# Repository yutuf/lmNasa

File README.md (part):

# LunaNav — where and when should we land on the Moon?

Open-source planning tool for landing sites and dates at the lunar south pole: describe a mission, and LunaNav
searches the real terrain hour by hour and tells you where and when a solar lander survives. Then stand on the
lander, or drive a rover there.

Two interfaces: **Simple** (pick a mission and a month, get the top sites as cards, open a site's profile) and
**Advanced** (every requirement, the tables, charts, the Artemis comparison and exports); switch at the top.

## In 30 seconds

**The problem.** At the lunar south pole the Sun skims the horizon, so a few hundred metres decide whether a lander
has power, can talk to Earth, can touch down safely, and is near water ice. Today, answering *"where and on which
date do we land?"* takes several expert tools.

**What LunaNav does.** Pick a mission (or describe it to the guide). In a few seconds it checks **21,856 points × every
landing date × every hour** against NASA LOLA terrain and JPL DE440, and ranks where the mission survives:

- **Survives:** sunlight, Earth contact (with a free NASA DSN dish), the longest darkness, and a battery model.
- **Lands safely:** 95 % of the touchdown zone (100 m to 1 km) is gentler than a limit, from LOLA 40 m slopes.
- **Worth it:** the distance to the nearest *ice cold trap* (permanent shadow where Diviner puts ice within 1 m).
- **Gets there:** a spacecraft route from Earth to a polar orbit to the descent, approaching with the Sun behind it.

**One number.** Under a 14-day robotic-lander mission in September 2027, **every centre of NASA's Artemis III
regions inside the search area fails a terrain check, and LunaNav finds landable points 4–13 km away in five of
them.**

**Checked, not assumed.** Sunlight against NASA's own maps (median +1.9 points, r = 0.96); touchdown slopes against
LOLA's official 40 m slope map (median 1.15°, r = 0.94, 6,620 points); this browser engine against the Python
reference (18 cases identical). The full list is in the app under *Method & data*.

### Built during NASA Space Apps 2026 (14–15 Nov)

The project existed before the event: everything up to the git tag `pre-hackathon` (the site search, horizons,
lander and rover views, and the Python planner). Added during the event, all on top of that tag:

| Added | Where |
|---|---|
| Touchdown zone check (LOLA 40 m slopes, 100 m to 1 km zones), validated against LOLA's slope map | `scripts/build_hazard.py`, `web/src/engine.ts` |
| Water ice: distance to the nearest ice cold trap and cold-trap area within 5 km | `scripts/build_science.py` |
| Survival-vs-science chart with the best trade-offs | `web/src/components/TradeOff.tsx` |
| Six mission scenarios, and a simulation that compares them side by side | `web/src/scenarios.ts` |
| Spacecraft route on the globe, with the approach direction chosen against the Sun | `web/src/flight.ts` |
| Artemis III head-to-head: each region's centre against the best point inside it | `web/src/artemis.ts` |
| Ask Luna works with no AI key (an offline guide, EN/TR); Gemini when a key is set | `web/src/lunaLocal.ts` |
| Validation panel, launch window, 3-step guide; zone, ice and approach in the CSV and report | `web/src/App.tsx`, `web/src/report.ts` |

The plan and progress log: [docs/HACKATHON_PLAN.md](docs/HACKATHON_PLAN.md). A 2-minute demo script for the web app: [docs/DEMO_WEB.md](docs/DEMO_WEB.md).

## The web app (`web/`)

```bash
cd web && npm install && npm run dev        # http://localhost:5173
```

Static site (Vite + React + three.js) with one optional serverless function for the AI guide; deploys to Vercel
with root directory `web` (set `GEMINI_API_KEY` for the AI guide). Everything else runs in the browser, offline.

**Search, not a spot picker.** Set the mission (length, minimum sunlight and Earth contact, longest darkness,
battery, steepest ground, whether Earth contact also needs a free NASA DSN dish) and a landing window. A Web
Worker engine checks all 21,856 points of a 2 km grid around the south pole, every landing date in the window,
hour by hour against each point's real LOLA horizon (about 12 million hourly checks in about a second), and
ranks the sites. The same algorithm as the Python package, checked against it case by case (`web/src/*.test.ts`).

- **Results:** a ranked table with place names from the IAU gazetteer ("SE rim of Shackleton", "on Mons
  Malapert"), the share of landing dates that pass, and the Artemis III region each site falls in; CSV export
  and a printable report; tick two to four rows to compare them side by side.
- **Site detail:** a GO / NO-GO verdict with the reason in one sentence; sunlight, Earth contact, longest
  darkness and battery against the requirements; every landing date in the window; the mission's sunrises,
  sunsets and Earth link losses; better spots within 8 km; eclipses inside the mission (Earth hiding the Sun,
  checked against NASA's eclipse catalogue); what the lander sees, as a 360° horizon with the Sun and Earth
  moving over it; and a calendar of every landing date from November 2026 to the end of 2028.
- **Sunlight map:** scrub or play the mission and watch the shadows sweep across the pole.
- **Copy link:** the address keeps the mission and the chosen site.
- **Ask Luna:** describe a mission in your own words ("a 3-week rover landing in spring 2027 that must always
  reach Earth") or ask about the results; an AI guide (Google Gemini, server-side key) sets up the search or
  explains the numbers, using only what the engine computed. English and Turkish throughout.

**Be there.** From any result, *Stand on the lander* or *Drive a rover here*:

- Real LOLA terrain: 10 m maps from NASA's 5 m/px LOLA site models (Barker et al. 2021) at 15 landing areas,
  the 200 m polar grid elsewhere, lunar curvature included; NASA 3D models (Apollo LM, rover, LRO).
- The Sun and Earth where the ephemeris puts them for that date; ridges cast real shadows (a horizon ray-march
  per vertex for distant ridges, a shadow map nearby); dashed paths show where the Sun and Earth travel during
  the mission.
- A survival game with honest physics: battery, solar input and power use, countdowns to sunset and Earth-set,
  radio link through the DSN, time warp to an hour per second. The rover power figures are illustrative and
  labelled as such.
- A VIPER-style objective: drive to the most ice-favourable permanently shadowed spot nearby (NASA permanent
  shadow map, USGS ice index, Diviner temperatures and ice stability depth), drill for two hours, and bring the
  sample back into sunlight before the battery runs out. A route planner (A* over the terrain, rover slope
  limit, prefers sunlit ground) with an autopilot.
- Keyboard and game controller; a USB LED ring can mirror the rover's sky live ([hardware/sky_link](hardware/sky_link)).

### Data in the web app

| What | Source |
|---|---|
| Terrain horizons, 21,856 points | NASA LRO LOLA polar DEMs (PDS), `scripts/build_horizon_atlas.py` |
| Sun and Earth, hourly | JPL DE440 via Skyfield, Moon-fixed, Earth parallax per point |
| Deep Space Network visibility | Goldstone, Madrid, Canberra, 10° mask |
| 10 m rover terrain | LOLA 5 m/px site DEMs, Barker et al. 2021 (NASA GSFC PGDA product 78) |
| Permanent shadow, average Sun/Earth visibility | Mazarico et al. 2011 (PGDA product 69) |
| Ice favorability index | USGS Astrogeology |
| Surface temperature, ice stability depth | LRO Diviner Polar Resource Product (Paige et al., PDS) |
| Place names | IAU Gazetteer of Planetary Nomenclature (USGS) |
| Artemis III regions | NASA / USGS candidate region outlines |
| 3D models | NASA 3D Resources (`web/public/models/CREDITS.md`) |
| Regolith texture | NASA Artemis south-pole simulation kit (USGS 84S project) |

## The Python package and planner (`lunanav/`, `app.py`)

The science lives in a tested Python package; the original Streamlit planner (live at
https://limitlessapps.streamlit.app/) remains for detailed analysis. Demo video of the planner:
[docs/demo/lunanav-demo.mp4](docs/demo/lunanav-demo.mp4).

Existing tools (QuickMap, Moon Trek, JPL Horizons) are built for detailed analysis.
Answering a simple planning question — *"at this south-pole site, on which dates do we
have Sun and Earth in view, and does the lander survive the night?"* — takes many steps
and expert knowledge. LunaNav answers it in one screen:

- **All nine NASA Artemis III candidate regions** (USGS grids) plus published candidate points, each with
  its source.
- **Score heatmap:** every candidate site × every start date, bright = go (colour-blind-safe), readable
  on a phone; filter by site group.
- **Real terrain horizon:** Sun and Earth are compared against the actual LOLA horizon, not a flat one.
- **Battery survival:** a transparent lander power model shows *when* a mission would die.
- **Battery sizing:** the smallest battery that survives the chosen mission (exact for the model),
  plus a GO / NO-GO verdict in plain words and the score broken down term by term.
- **360° view from the lander:** the terrain silhouette with the Sun's and Earth's paths over the
  mission, plus a time slider — *"on day 5, is the Sun up, and when does it set?"*
- **Communication windows:** when Earth is above the terrain, and when it next sets or rises.
- **English / Türkçe:** a switch at the top translates the simple view (the planner stays in English);
  `?lang=tr` opens the page in Turkish.
- **Anywhere on the Moon:** a whole-Moon relief map and 16 landed missions (Luna 9 to Blue Ghost 1,
  `data/landed_missions.yaml`); outside the south pole the horizon is traced from LOLA's global grid
  (`data/global_grid.npz`, 1.9 km). Sun and Earth tracks are rotated from a computed site with Earth's parallax
  corrected from the hourly Earth-Moon distance (`lunanav/anywhere.py`): checked against independent DE440 runs
  2,700 km away, within 0.018° (without the parallax correction Earth would be off by 0.33°); `tests/test_anywhere.py`.
- **Any point near the pole:** pick a spot south of 84.5°S on a LOLA relief map (or type its coordinates); the
  app traces its horizon on the spot from a compact 200 m / 800 m LOLA grid (`data/polar_grid.npz`, 5 MB) and
  rotates the Sun/Earth track from the nearest computed site. Against the full-resolution horizons at 27 sites:
  sunlit share within 0.5 points (median, worst 4.1), Earth in view within 0.0 (median, worst 13.9 on a narrow
  crest); `tests/test_polar_grid.py`.
- **Deep Space Network check:** Earth above the lander's horizon is not enough; one of NASA's DSN complexes
  (Goldstone, Madrid, Canberra) must also see the Moon. Precomputed hourly (`data/dsn.npz`): each complex sees
  the Moon above 10° about 41 % of the time, at least one of them 98.3 % of the time.
- **Simple view first:** the page opens on one question, five landing spots, a large GO / NO-GO with the reason in
  one sentence, a day-by-day strip, what happens if the launch slips (1 day to 1 month), the same date at the
  other spots, and an animation of the Sun and Earth moving along the real horizon, and a 3D view of the 40 × 40 km of terrain
  around the lander with the shadows the Sun casts at any hour of the mission (`data/terrain/`, cut from LOLA
  by `scripts/make_terrain_patches.py`; shadows from terrain inside the patch only, see `lunanav/terrain3d.py`).
- **Cited vs derived points:** every site comes from a publication: a published point, or the centre of an official
  Artemis III region computed from the USGS grid (source shown).
  Next to it LunaNav can show a **derived** point (the best spot within 1 km on a gentle slope) and, for
  Artemis III regions, the **best point in the whole region**. Always labelled, never a replacement for
  the cited one.
- **South-pole map** of the sites and NASA's nine Artemis III candidate regions (exact USGS grid
  outlines), true to scale, with the Earth-facing side marked.
- **Shareable links:** the page address always encodes the scenario (settings, which site groups are shown,
  site, start date).
- **CSV export** of any mission: hourly Sun/Earth position, terrain, visibility and battery.
- **Plain-language help** in the app for students, educators and the public, and four ready-made
  classroom activities with answers: [docs/EDUCATORS.md](docs/EDUCATORS.md).
- **2-minute demo script** with a link per scene, every verdict checked in CI: [docs/DEMO.md](docs/DEMO.md).
- **Physical twin** (design stage, not yet manufactured): a true-scale 3D-printable relief of Malapert
  Massif with the three demo points, and a 24-LED "horizon compass" PCB that replays a site's Sun and
  Earth directions from LunaNav's data: [hardware/README.md](hardware/README.md).

## Results at a glance

Data: JPL DE440 + LOLA terrain, hourly, 1 Nov 2026 – 31 Dec 2028; "Sun+Earth" = share of hours with at
least half the Sun's disk and Earth's centre above the terrain, seen from a 2 m mast.

- **All nine NASA Artemis III candidate regions are covered** (USGS grids), plus published points
  (Shackleton connecting ridge, de Gerlache rim, Malapert, IM-2 on Mons Mouton) and Apollo 11 for reference.
- **Region centres are poor stand-ins:** Sun+Earth at the centres ranges from 2 % (Slater Plain) to 28 %
  (Nobile Rim 2). Searching each whole region finds ground with **35 % to 84 %** on slopes ≤ 6°, best at
  Malapert Massif (83.6 %, Earth in view all the time), then Mons Mouton (72.5 %) and Nobile Rim 1 (67.9 %).
- **Terrain beats latitude:** at Malapert, moving 447 m from the published point takes Earth visibility
  from 44 % to 100 %.
- **Checked against NASA's independent maps** (Mazarico et al. 2011): for points nobody optimised the
  median difference is +1.9 points (r = 0.957 over 32 points). LunaNav's best-in-region values are
  matched by NASA's own values within ~100 m (median +0.5 points), since the two terrain models place
  narrow crests slightly differently; read them as the upper end of what NASA's maps support. One Earth
  value (Mons Mouton best point, 60 m map) is still unexplained.
- **Found along the way:** the IM-2 landing point lies in the Mons Mouton *Plateau* region, not the
  Mons Mouton one; NASA's regions overlap (e.g. 136 km² shared by Mons Mouton and the Plateau).
- **Limits:** illustrative lander (not a real spacecraft); slope from a 40 m map, so boulders and small
  craters are invisible; no thermal model or relay satellites.

## How it works

```
offline (needs kernels + DEM)                           runtime (Streamlit, light)
──────────────────────────────                          ──────────────────────────
LOLA south-pole DEM ──► build_horizons.py ──► data/horizons.json ─┐
                                                                  ├─► precompute.py ──► data/series/<site>.npz ──► app.py
NAIF kernels (DE440 + Moon frames) ──► lunanav.ephemeris ─────────┘                         (scoring, battery, plots)
                                                                                     │
LOLA DEM + data/series/<cited>.npz ──► derive_best_points.py ──► data/derived_sites.yaml + <site>_derived.npz
USGS Artemis III grids ──► artemis_regions.py ──► region centres (sites.yaml) + outlines (artemis_regions.json)
LOLA DEM + USGS grids + series ──► derive_region_best.py ──► <site>_region_best (derived_sites.yaml + .npz)
```

`derive_best_points.py` needs only the DEM: the Sun and Earth are so far away that moving
1 km on the Moon changes their direction by < 0.0002°, so the cited site's Sun/Earth alt-az series is
rotated into each candidate's local frame instead of re-running the ephemeris. (Checked against
independent DE440 runs: reprojecting Shackleton ridge → de Gerlache rim, ~25 km, matches to 0.0005° in
altitude.)

The app never touches the DEM or the kernels: everything it reads is committed under `data/`, so it
runs from a plain `pip install -r requirements.txt` with no secrets or API keys (see [Deploy](#deploy)).

| module | job |
|---|---|
| `lunanav/geometry.py` | great-circle steps, elevation angle with lunar curvature, visible disk fraction |
| `lunanav/horizon.py` | ray-march DEM → 360° horizon profile per site |
| `lunanav/ephemeris.py` | Skyfield: Sun/Earth alt-az from a point in the Moon's ME frame (with libration) |
| `lunanav/visibility.py` | Sun disk fraction above terrain, Earth above terrain |
| `lunanav/power.py` | battery state-of-charge simulation |
| `lunanav/metrics.py` | window metrics, constraints, score, vectorised start-date scan, delay tolerance, set/rise timers |
| `lunanav/panorama.py` | azimuth helpers for the 360° view (circular mean, unwrap, compass ticks) |
| `lunanav/derive.py` | candidate grid, slope, alt-az reprojection, ranking for derived points |
| `lunanav/outlines.py` | region outlines at runtime (pure numpy): which Artemis III region(s) contain a point |
| `lunanav/regions.py` | USGS region grids: exact inside/outside test, grid points, projection |
| `lunanav/sites.py` | cited sites (`data/sites.yaml`) + generated derived points (`data/derived_sites.yaml`) |
| `app.py` | Streamlit UI |

| script (offline) | needs | writes |
|---|---|---|
| `scripts/fetch_kernels.py` | internet (NAIF) | `data/kernels/` (DE440 + Moon frames) |
| `scripts/build_horizons.py` | LOLA DEM | `data/horizons.json` |
| `scripts/precompute.py` | kernels + `horizons.json` | `data/series/<site>.npz` |
| `scripts/derive_best_points.py` | LOLA DEM + series | `data/derived_sites.yaml`, `<site>_derived.npz`, horizons |
| `scripts/artemis_regions.py` | USGS grid shapefiles | Artemis III region centres in `data/sites.yaml` |
| `scripts/derive_region_best.py` | LOLA DEM + USGS grids + series | best point inside each region (`<site>_region_best`) |
| `scripts/mazarico_compare.py` | NASA PGDA illumination + PSR maps | `data/mazarico.json`: independent check + nearest permanent shadow |
| `scripts/check_map_alignment.py` | two NASA maps | best registration shift between them (diagnostic) |
| `scripts/make_demo_series.py` | nothing | synthetic series for UI work only (clearly flagged in the app) |
| `scripts/make_global_grid.py` | LOLA `ldem_16.img` | `data/global_grid.npz` for horizons anywhere |
| `scripts/precompute_earth_distance.py` | kernels | `data/earth_distance.npz` for Earth parallax |
| `scripts/make_polar_grid.py` | LOLA 85°S 40 m + 80°S 80 m `.img` | `data/polar_grid.npz` for horizons at any point |
| `scripts/make_terrain_patches.py` | LOLA 85°S 40 m `.img` | `data/terrain/<site>.npz` for the 3D view |
| `scripts/precompute_dsn.py` | kernels | `data/dsn.npz`: Moon elevation at the three DSN complexes, hourly |
| `scripts/make_relief.py` | PDS LOLA polar `.img` | 3D-printable terrain tile (`hardware/relief/*.stl` + site positions) |
| `scripts/export_compass_track.py` | a site's series | LED animation for the horizon compass (`firmware/track.h`) |

## Quick start

```bash
python -m venv .venv && source .venv/bin/activate
pip install -e ".[offline,dev]"
pytest -q          # unit tests, an app smoke test, and integrity checks on the committed data

# real data
python scripts/fetch_kernels.py                          # ~130 MB (DE440)
python scripts/build_horizons.py data/dem/<lola_south_pole>.tif
python scripts/precompute.py      # default window 2026-11-01 → 2028-12-31 23:00 UTC (--end 2029-01-01 is exclusive)
python scripts/derive_best_points.py data/dem/LDEM_80S_40MPP_ADJ.TIF   # optional: derived points

# or synthetic data just to work on the UI
python scripts/make_demo_series.py

streamlit run app.py
```

## Deploy

**Web app (Vercel, free):** import `yutuf/lmNasa` at https://vercel.com/new, set *Root Directory* to `web`
(Vite is detected; build `npm run build`, output `dist`), and add the environment variable `GEMINI_API_KEY`
(a free key from https://aistudio.google.com) for the Ask Luna guide; without it everything except Luna works.
Locally the key goes in `web/.env.local` (git-ignored).

**Streamlit planner:** the planner runs on Streamlit Community Cloud at **https://limitlessapps.streamlit.app/**, deployed from this repo's `main` branch.
Locally: `streamlit run app.py`, then open `http://localhost:8501/`.

To deploy a copy (free; needs a GitHub account, and the sign-in can only be done by a person):

1. Sign in at https://share.streamlit.io with GitHub and allow access to `yutuf/lmNasa`.
2. Create app → repository `yutuf/lmNasa`, branch `main`, main file `app.py`.
3. Under Advanced settings pick Python 3.13 (what CI tests); no secrets are needed.
4. Deploy. Dependencies come from `requirements.txt`; the app imports `lunanav/` from the repo root.

## Adding sites

Every site needs a source. Two ways in:

1. **A published point:** add it to `data/sites.yaml` with `source:` (link) and `verified: true` once the
   numbers are copied from that source.
2. **NASA's Artemis III candidate regions** (published as areas of ~20 × 20 km and larger, not points):
   download the USGS navigation grids ([McClernan 2024, doi:10.5066/P1MEQ6UK](https://doi.org/10.5066/P1MEQ6UK)),
   unzip, then `python scripts/artemis_regions.py <folder> --outlines` (`--outlines` also writes the
   region outlines the map draws, `data/artemis_regions.json`). It adds the area-weighted centre of each
   region's 1 km grid as a site, labelled *region centre* (Malapert Massif keeps its published point,
   which lies inside its region; the IM-2 point is inside the Mons Mouton *Plateau* region, so it does
   not stand in for the Mons Mouton region).

Then rebuild the data for the new sites (needs the DEM and kernels):

```bash
python scripts/build_horizons.py data/dem/LDEM_80S_40MPP_ADJ.TIF --sites <new ids>      # other profiles kept
python scripts/precompute.py --sites <new ids>                                          # other series kept
python scripts/derive_best_points.py data/dem/LDEM_80S_40MPP_ADJ.TIF --sites <new ids>
```

Without `--sites` every site is recomputed. `precompute.py --end` is exclusive.

## Scoring

For one site and one start date, over the mission duration (1 h steps):

- **sunlit** = share of hours with ≥ 50 % of the solar disk above terrain
- **Earth in view** = share of hours with Earth's center above terrain
- **longest shadow** = longest continuous run of non-sunlit hours
- **battery margin** = (min state of charge − failure line) / (1 − failure line)

`score = 100 × (0.4·sunlit + 0.3·Earth + 0.3·battery margin)`.
If any constraint fails (min sunlit, min Earth, max shadow, battery), the score is ×0.25 and the
reasons are listed. Constraints are editable in the sidebar; the weights live in `MissionConstraints`.

Ties at the top are broken by **delay_ok_days**: how many days the launch can slip with every
later start still feasible.

## Derived points

For each cited, non-reference site: a grid of candidates (100 m spacing) within 1 km, candidates
steeper than 10° (40 m baseline) dropped, a full 360° horizon for each, then ranked by the share of
hours with the Sun (≥ 50 % of the disk) **and** Earth in view; tie-break on sunlight. The cited point
is recomputed with the same DEM and settings so the comparison is fair. If no candidate beats the
cited point, no derived point is written. All three numbers are command-line options.

Result with LOLA `LDEM_80S_40MPP_ADJ`, 2026-11-01 → 2028-12-31 (share of hours):

| cited site | cited: Sun+Earth / Sun / Earth / slope | derived point | derived: Sun+Earth / Sun / Earth / slope |
|---|---|---|---|
| Shackleton connecting ridge | 51.8 % / 91.1 % / 53.9 % / 0.7° | — (cited point is already the best) | — |
| de Gerlache rim (site 011) | 41.3 % / 77.3 % / 57.3 % / 3.4° | 200 m W | 48.8 % / 85.2 % / 57.3 % / 1.6° |
| Malapert Massif | 15.8 % / 42.3 % / 44.1 % / **10.5°** | 447 m NE | 66.8 % / 66.8 % / 100 % / 3.9° |
| Mons Mouton (IM-2) | 38.6 % / 45.5 % / 82.1 % / 2.5° | 825 m S | 43.9 % / 51.5 % / 83.7 % / 1.6° |

The Malapert point is published only to whole degrees (86°S, 0°E: ±0.5° ≈ ±15 km in latitude,
≈ ±1 km in longitude at 86°S), so a 447 m move is well inside its own uncertainty; its cited
coordinate is also steeper than our 10° limit, which the app flags.

**Artemis III region centres** (centre of each region's USGS 1 km grid; Malapert Massif uses its
published point above, which lies inside its region. The IM-2 point above lies in the Mons Mouton
*Plateau* region, so the Mons Mouton region has its own centre):

| region centre | centre: Sun+Earth / Sun / Earth / slope | derived point | derived: Sun+Earth / Sun / Earth / slope |
|---|---|---|---|
| Peak near Cabeus B | 9.1 % / 37.9 % / 28.8 % / **12.0°** | 943 m NE | 48.3 % / 63.8 % / 77.0 % / 6.8° |
| Mons Mouton Plateau | 20.2 % / 26.1 % / 66.7 % / 2.1° | 1000 m SW | 40.3 % / 46.3 % / 84.7 % / 8.4° |
| Nobile Rim 2 | 28.1 % / 40.8 % / 65.1 % / 4.7° | 1000 m NE | 31.7 % / 46.6 % / 66.0 % / 7.0° |
| Nobile Rim 1 | 9.4 % / 29.2 % / 32.2 % / **16.9°** | 985 m SE | 26.5 % / 50.2 % / 48.1 % / 5.7° |
| de Gerlache Rim 2 | 21.7 % / 37.2 % / 51.3 % / **11.3°** | 500 m NW | 22.0 % / 37.5 % / 51.3 % / 10.0° |
| Haworth | 6.1 % / 10.0 % / 39.6 % / 2.9° | 1000 m SE | 20.7 % / 36.7 % / 50.9 % / 7.2° |
| Slater Plain | 2.0 % / 2.3 % / 36.7 % / 3.4° | 1000 m SE | 9.6 % / 21.5 % / 40.6 % / 9.8° |
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
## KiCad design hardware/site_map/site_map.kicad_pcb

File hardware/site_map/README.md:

# Site map: a PCB map of the lunar south pole

A 100 x 100 mm two-layer board. The silkscreen is a south polar stereographic map with the nine
Artemis III candidate regions, and one WS2812B LED sits at each region's best landing point as computed
by LunaNav (`data/derived_sites.yaml`), plus two published points from `data/sites.yaml`. Firmware, which
does not exist yet, is meant to colour each LED by the GO / NO-GO verdict for a chosen landing date.

Nothing here has been manufactured or powered.

## Rebuild

```
"C:/Program Files/KiCad/10.0/bin/python.exe" hardware/site_map/generate_board.py
cd hardware/site_map
kicad-cli pcb drc --refill-zones --save-board --severity-error --severity-warning --output drc_report.txt site_map.kicad_pcb
kicad-cli pcb render --output render_top.png --side top --width 1400 --height 1400 --quality high --background opaque site_map.kicad_pcb
kicad-cli pcb export step --subst-models --force -o site_map.step site_map.kicad_pcb
```

There is no schematic: `generate_board.py` is the netlist. It places the parts, routes the board with its
own grid router, draws the silkscreen and writes `led_sites.json`. `site_map.kicad_pro` is the file
kicad-cli created with its defaults; no rule or severity in it was edited.

## Map

- Projection: south polar stereographic on a sphere of radius 1737.4 km, r = 2 R tan((90 + lat) / 2),
  x = r sin(lon), y = r cos(lon). Longitude 0 (Earth side) points up, 90 E points right.
- Scale 1:4,000,000 (4 km per mm). The pole is at (53.0, 53.0) mm from the board's top-left corner.
- Check: the published Malapert point (86.0 S, 0 E) projects to x = 0.000 km, y = +121.343 km, straight
  above the pole.
- The nine region outlines span 89.3 x 59.4 mm on the board; margins to the board edge are 5.46 mm left,
  8.73 mm top, 5.25 mm right.
- Silkscreen: region outlines, dashed latitude circles at 85 S and 88 S with labels, a cross at the pole,
  an EARTH arrow pointing up, a 50 km scale bar (12.5 mm), the scale, the title, one label per LED.

## LEDs

Chain: J1 pin 2 (DIN) -> R1 330 ohm -> D1 ... D11 -> J2 pin 2 (DOUT). Chain index = D number - 1.
Positions in mm from the board's top-left corner. The full table with lat, lon and true positions is in
`led_sites.json`.

| Ref | Site id | Placed (mm) | Offset from true position |
| --- | --- | --- | --- |
| D1 | shackleton_ridge (published) | 50.11, 56.12 | 0 |
| D2 | de_gerlache_rim (published) | 51.99, 47.16 | 8.60 mm = 34.4 km |
| D3 | artemis_de_gerlache_rim_2_region_best | 43.09, 48.95 | 0 |
| D4 | artemis_peak_near_cabeus_b_region_best | 7.89, 35.30 | 0 |
| D5 | artemis_haworth_region_best | 42.14, 27.67 | 0 |
| D6 | malapert_massif_region_best | 51.77, 22.44 | 0 |
| D7 | artemis_mons_mouton_region_best | 66.15, 23.90 | 5.20 mm = 20.8 km |
| D8 | artemis_nobile_rim_1_region_best | 75.12, 22.97 | 0 |
| D9 | artemis_mons_mouton_plateau_region_best | 84.68, 20.44 | 0 |
| D10 | artemis_nobile_rim_2_region_best | 90.74, 29.19 | 0 |
| D11 | artemis_slater_plain_region_best | 69.26, 65.67 | 0 |

Two LEDs are not on their true position, because the generator keeps LED centres at least 9.0 mm apart
(room for the 100 nF capacitor and vias of each LED; the smallest distance on the board is 9.02 mm):

- D7, Mons Mouton region best: moved 20.8 km. A leader line runs to a dot at the true position, which is
  just left of D8. One silkscreen line of D8's footprint was removed so that it does not touch the dot.
- D2, published de Gerlache rim point: moved 34.4 km. Its true position lies under D3 (the de Gerlache
  Rim 2 region-best LED), so no dot can be drawn; the leader line ends at D3.

## Electrical

- 11 x WS2812B 5050, 11 x 100 nF 0603 (one next to each LED's VDD pad), R1 330 ohm 0603 in series with
  the data input, J1 1x3 2.54 mm header (5V, DIN, GND) and J2 1x3 header (5V, DOUT, GND) at the bottom
  edge, 4 M3 holes 5 mm in from the corners.
- Data chain: 217.5 mm of 0.25 mm track in 13 nets, all on the front layer, no vias, longest hop 38.5 mm.
- +5V: 0.5 mm stubs on the front, one via per LED, and a 0.8 mm bus on the back layer in chain order from
  J1 to J2 (268.1 mm).
- GND: pours on both layers, two GND vias per LED.
- DRC (`drc_report.txt`, errors and warnings): 0 violations, 0 unconnected items.

## Not verified, and known weaknesses

- Nothing has been built, soldered or powered. No firmware exists for this board.
- At this scale a typical region is only a few millimetres across, smaller than the 5 mm LED sitting in
  it. Silkscreen lines are cut where they cross pads and footprint outlines, so most region outlines are
  partly or fully hidden under their LED in `render_top.png`. A larger board or smaller LEDs (2020 size)
  would be needed to show every outline in full.
- The LED labels carry short names (for example "DG RIM 2"); the regions have no separate name labels.
- The pole cross is cut short where it meets D1's pad.
- The +5V bus is a single 0.8 mm daisy chain, not checked for voltage drop with all 11 LEDs at full white
  (roughly 0.66 A by the usual 60 mA per LED figure, which is a datasheet-level assumption, not measured).
- The script reads the YAML files with its own small parser (KiCad's Python has no PyYAML); the result was
  not cross-checked against PyYAML.
- The STEP file was exported but not opened in a CAD program. `--subst-models` was used; whether every
  part has a 3D model in it was not checked.
- Only the top render was inspected. The back layer was checked by DRC only.

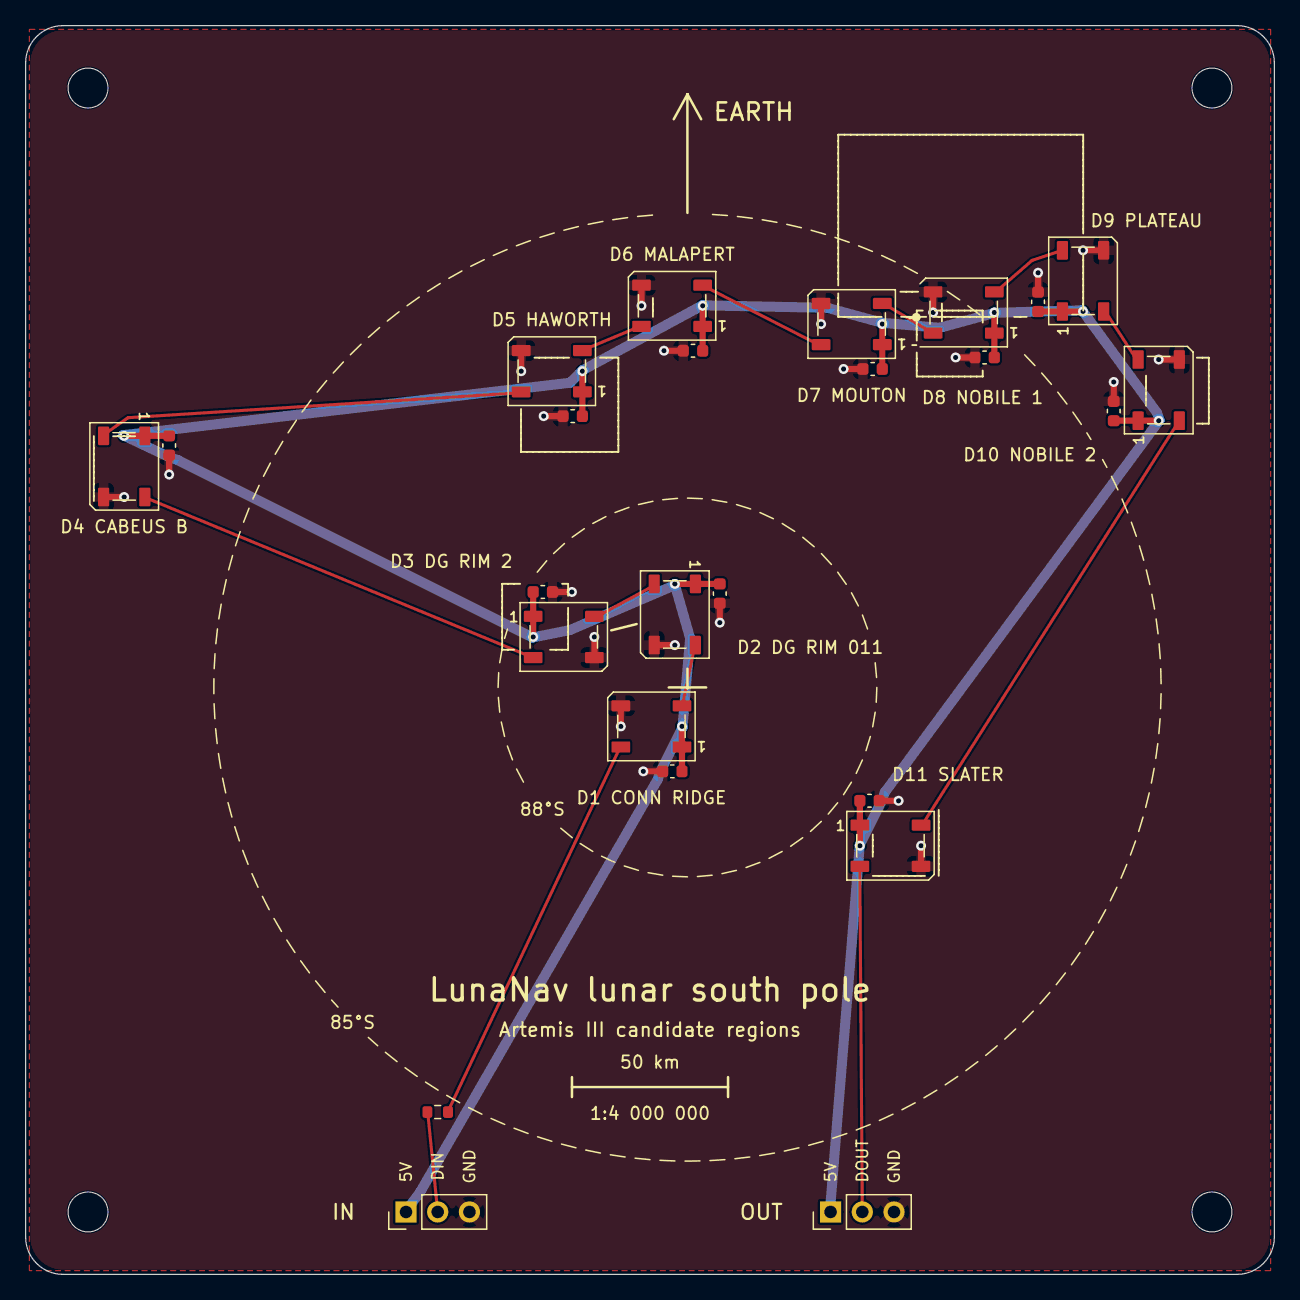
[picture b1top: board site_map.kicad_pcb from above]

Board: 2 copper layers, 100.0 x 100.0 mm, 29 parts (0 on the bottom side), 15 nets.

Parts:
C1, C2, C3, C4, C5, C6, C7, C8, C9, C10, C11: 100n; C_0603_1608Metric
D1, D2, D3, D4, D5, D6, D7, D8, D9, D10, D11: WS2812B; LED_WS2812B_PLCC4_5.0x5.0mm_P3.2mm
H1, H2, H3, H4: M3; MountingHole_3.2mm_M3
J1: IN; PinHeader_1x03_P2.54mm_Vertical
J2: OUT; PinHeader_1x03_P2.54mm_Vertical
R1: 330R; R_0603_1608Metric

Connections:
+5V: C1.2, C2.2, C3.1, C4.2, C5.2, C6.2, C7.2, C8.2, C9.1, C10.1, C11.1, D1.1, D2.1, D3.1, D4.1, D5.1, D6.1, D7.1, D8.1, D9.1, D10.1, D11.1, J1.1, J2.1
DATA_IN: J1.2, R1.1
DATA_OUT: D11.2, J2.2
GND: C1.1, C2.1, C3.2, C4.1, C5.1, C6.1, C7.1, C8.1, C9.2, C10.2, C11.2, D1.3, D2.3, D3.3, D4.3, D5.3, D6.3, D7.3, D8.3, D9.3, D10.3, D11.3, J1.3, J2.3
LED_D0: D1.4, R1.2
LED_D1: D1.2, D2.4
LED_D2: D2.2, D3.4
LED_D3: D3.2, D4.4
LED_D4: D4.2, D5.4
LED_D5: D5.2, D6.4
LED_D6: D6.2, D7.4
LED_D7: D7.2, D8.4
LED_D8: D8.2, D9.4
LED_D9: D9.2, D10.4
LED_D10: D10.2, D11.4

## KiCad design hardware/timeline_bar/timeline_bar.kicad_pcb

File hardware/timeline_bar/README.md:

# Timeline bar (PCB)

The app's central comparison as light: three rows of 28 addressable LEDs. A row is one landing spot,
an LED is one Earth day of a 28-day window. Each LED mixes yellow (share of that day's hours with at
least half the solar disk above the terrain) and blue (share of that day's hours with Earth above the
terrain). The three rows are the three demo spots at Malapert Massif, all within 5 km of each other:

| row | site id | what |
|---|---|---|
| A | `malapert_massif` | published point |
| B | `malapert_massif_derived` | 447 m away |
| C | `malapert_massif_region_best` | best in region, 5 km west |

The board has no controller. 5 V and data come in on J1 at the left edge and leave on J2 at the right
edge. **Nothing here has been manufactured, and the firmware has never been compiled.**

## The board

- 215 x 45 mm rectangle, 2 layers, 4 M3 holes (3.2 mm drill) 4 mm in from each corner
- D1-D84 WS2812B (5050) on a 7.0 mm pitch, rows 11.0 mm apart; day 1 is the left column
- C1-C84 100 nF 0603, one per LED, its +5V pad 1.95 mm (centre to centre) from the LED's VDD pad
- C85-C90 10 uF 0805, one at each end of each row
- R1 330 ohm 0603 in the data line between J1 and D1
- J1 (input, left edge) and J2 (output, right edge): 1x3 2.54 mm pin headers
- Silkscreen: title, legend (yellow = Sun, blue = Earth, 1 LED = 1 Earth day), day numbers 1, 7, 14,
  21, 28 under the columns, row letters A, B, C at the right end and their meaning along the bottom
  edge. LED and capacitor designators are hidden: there is no room on a 7 mm pitch.

| header | pin 1 | pin 2 | pin 3 |
|---|---|---|---|
| J1, pin 1 lowest | 5V | DIN (to R1, then D1) | GND |
| J2, pin 1 highest | 5V | DOUT (from D84) | GND |

### LED chain order

One serpentine chain. `scripts/export_timeline_track.py` uses the same order (both files carry the
same `chain_index` function).

| chain index | LEDs | row | direction |
|---|---|---|---|
| 0-27 | D1-D28 | A | day 1 to 28, left to right |
| 28-55 | D29-D56 | B | day 28 to 1, right to left |
| 56-83 | D57-D84 | C | day 1 to 28, left to right |

So D1 = row A day 1, D28 = row A day 28, D29 = row B day 28, D56 = row B day 1, D57 = row C day 1,
D84 = row C day 28. Reading the saved board back confirms that DOUT of every LED is on the same net as
DIN of the next, D1's DIN goes to R1 and D84's DOUT to J2.

### Numbers printed by the generator and read back from the saved board

- LED orientation: rows A and C 180 degrees, row B 0 degrees (chosen by measuring the pads so DIN
  faces the previous LED)
- Data hop inside a row: 3.91 mm. Row A to B at the right end: 13.90 mm with 2 vias (it crosses the
  shared +5V bus on the back layer). Row B to C at the left end: 14.10 mm on the front.
- +5V: one 1.5 mm bus between rows A and B (204.0 mm, shared by both rows) and one below row C
  (200.0 mm), joined by 1.5 mm vertical tracks at x = 7.5 mm and x = 207.5 mm. Each LED reaches its
  bus through a 0.5 mm stub via its 100 nF capacitor. J2's 5V pin hangs on a 4.0 mm long, 1.0 mm wide
  track.
- GND: pours on both layers, 186 vias in total of which 183 are ground (one per LED VSS pad, one per
  capacitor, 9 stitching vias below row C); the other 3 carry data.
- Data tracks 0.25 mm, ground stubs 0.4 mm.
- Nearest copper to a mounting hole: track centre 4.61 mm from the hole centre (the 1.5 mm +5V bus at
  the two lower holes), so copper starts 3.86 mm from the centre. The pours are kept out to a radius
  of 3.4 mm around each hole.
- KiCad 10.0.4 DRC (errors and warnings): 0 violations, 0 unconnected items. See `drc_report.txt`.

### Current limit: read this before powering it

A WS2812B draws about 20 mA per colour at full brightness, 60 mA at full white (typical datasheet
figure, not measured here). 84 x 60 mA = **5.04 A at full white**. That is far more than these tracks
or a USB port can carry: the IPC-2221 estimate for a 1.5 mm outer-layer track in 35 um copper at a
10 degree rise is 3.2 A, and for the 1.0 mm stub to J2 2.4 A.

Firmware must cap brightness. Worst case is every LED with all three colours at the cap (row C of the
default data is exactly that: Sun and Earth both at 100 % on all 28 days). Allowing 1 mA idle current
per LED (84 mA, also a typical figure):

    84 x 60 mA x cap/255 + 84 mA < 1000 mA   ->   cap <= 46 of 255 (18 %)

At 46 the worst case is 993 mA; at 47 it is 1,013 mA. With the default `track.h` and red = green =
sun share, blue = earth share, the same arithmetic gives 840 mA at cap 46 (4.19 A plus idle with no
cap). 1 A is still more than a plain USB 2.0 port (0.5 A) supplies: use a 5 V supply rated 1 A or more,
or lower the cap further.

## Rebuild

```bash
cd hardware/timeline_bar
"C:/Program Files/KiCad/10.0/bin/python.exe" generate_board.py
kicad-cli pcb drc --refill-zones --save-board --severity-error --severity-warning --output drc_report.txt timeline_bar.kicad_pcb
kicad-cli pcb render --output render_top.png --side top --width 2400 --height 600 --zoom 3.6 --quality high --background opaque timeline_bar.kicad_pcb
kicad-cli pcb export step --subst-models --force -o timeline_bar.step timeline_bar.kicad_pcb
```

The generator saves the ground pours unfilled; the DRC command fills them and saves the board.

## Data and firmware

`scripts/export_timeline_track.py` reads the precomputed hourly series of three sites and writes
`firmware/track.h`: `SUN_SHARE` and `EARTH_SHARE`, 84 values each, 0..255, in LED chain order.

```bash
python scripts/export_timeline_track.py                                    # the three spots above
python scripts/export_timeline_track.py site_a site_b site_c --start 2027-09-09 --days 28
```

Default run, 28 days from 2027-09-09 UTC:

| row | site | days with any Sun | mean Sun share | days with any Earth | mean Earth share |
|---|---|---|---|---|---|
| A | `malapert_massif` | 21 of 28 | 65.5 % | 13 of 28 | 42.9 % |
| B | `malapert_massif_derived` | 25 of 28 | 87.4 % | 28 of 28 | 100.0 % |
| C | `malapert_massif_region_best` | 28 of 28 | 100.0 % | 28 of 28 | 100.0 % |

`firmware/firmware.ino` (Adafruit NeoPixel) shows the picture once, with the cap of 46 built in.
**It has never been compiled or run.** The data pin number in it is a placeholder.

## Not verified

- Nothing has been manufactured, assembled or powered. DRC passing says the copper matches the script's
  netlist and KiCad's default rules, not that the board works.
- There is no schematic; the netlist lives in `generate_board.py`. The WS2812B pad mapping (1 VDD,
  2 DOUT, 3 VSS, 4 DIN) is KiCad's library footprint; it has not been compared with the datasheet of
  the exact LED that would be bought. Some 5050 variants differ.
- All current figures are arithmetic on typical datasheet values, not measurements. Copper thickness
  (35 um) is assumed. Voltage drop along the buses has not been simulated: by calculation one 204 mm
  bus is about 67 milliohm, and power enters at the left end only, so the right-hand LEDs will see a
  lower voltage and may look dimmer or redder at high brightness.
- 3.3 V data into 5 V WS2812B usually works but is out of spec; there is no level shifter on the board.
- Rows A and B share one +5V bus, so that bus carries two thirds of the current. The J1 pin, the cable
  and the supply have not been chosen or rated.
- Colour mixing is untested: whether yellow plus blue at high shares reads as "both" or just as white
  has to be judged on real LEDs, and the red/green balance for yellow is not tuned.
- The render is KiCad's 3D view of the layout, not a photo. `timeline_bar.step` was exported but not
  opened in a CAD program.
- The mounting holes have a 3.4 mm pour keep-out; a washer wider than 7.7 mm would reach the +5V bus
  at the two lower holes.

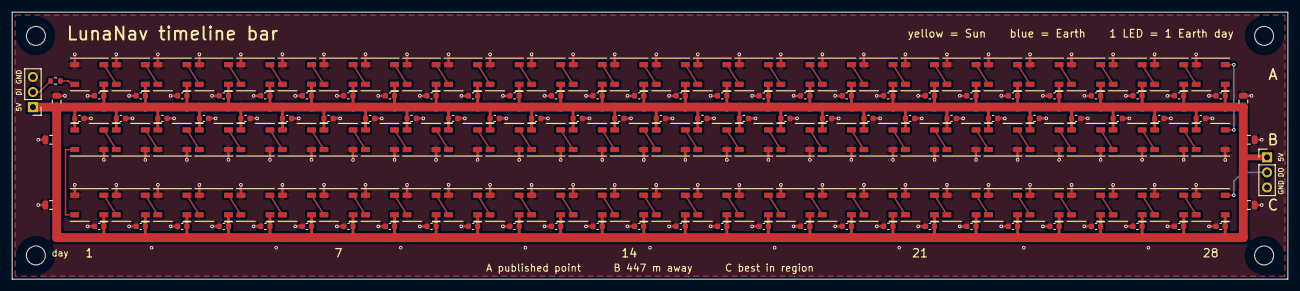
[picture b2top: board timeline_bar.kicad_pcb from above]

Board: 2 copper layers, 215.0 x 45.0 mm, 181 parts (0 on the bottom side), 88 nets.

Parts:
C1, C2, C3, C4, C5, C6, C7, C8, C9, C10, C11, C12, C13, C14, C15, C16, C17, C18, C19, C20, C21, C22, C23, C24, C25, C26, C27, C28, C29, C30, C31, C32, C33, C34, C35, C36, C37, C38, C39, C40, C41, C42, C43, C44, C45, C46, C47, C48, C49, C50, C51, C52, C53, C54, C55, C56, C57, C58, C59, C60, C61, C62, C63, C64, C65, C66, C67, C68, C69, C70, C71, C72, C73, C74, C75, C76, C77, C78, C79, C80, C81, C82, C83, C84: 100n; C_0603_1608Metric
C85, C86, C87, C88, C89, C90: 10u; C_0805_2012Metric
D1, D2, D3, D4, D5, D6, D7, D8, D9, D10, D11, D12, D13, D14, D15, D16, D17, D18, D19, D20, D21, D22, D23, D24, D25, D26, D27, D28, D29, D30, D31, D32, D33, D34, D35, D36, D37, D38, D39, D40, D41, D42, D43, D44, D45, D46, D47, D48, D49, D50, D51, D52, D53, D54, D55, D56, D57, D58, D59, D60, D61, D62, D63, D64, D65, D66, D67, D68, D69, D70, D71, D72, D73, D74, D75, D76, D77, D78, D79, D80, D81, D82, D83, D84: WS2812B; LED_WS2812B_PLCC4_5.0x5.0mm_P3.2mm
H1, H2, H3, H4: M3; MountingHole_3.2mm_M3
J1: IN: 5V DIN GND; PinHeader_1x03_P2.54mm_Vertical
J2: OUT: 5V DOUT GND; PinHeader_1x03_P2.54mm_Vertical
R1: 330R; R_0603_1608Metric

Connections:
+5V: C1.2, C2.2, C3.2, C4.2, C5.2, C6.2, C7.2, C8.2, C9.2, C10.2, C11.2, C12.2, C13.2, C14.2, C15.2, C16.2, C17.2, C18.2, C19.2, C20.2, C21.2, C22.2, C23.2, C24.2, C25.2, C26.2, C27.2, C28.2, C29.1, C30.1, C31.1, C32.1, C33.1, C34.1, C35.1, C36.1, C37.1, C38.1, C39.1, C40.1, C41.1, C42.1, C43.1, C44.1, C45.1, C46.1, C47.1, C48.1, C49.1, C50.1, C51.1, C52.1, C53.1, C54.1, C55.1, C56.1, C57.2, C58.2, C59.2, C60.2, C61.2, C62.2, C63.2, C64.2, C65.2, C66.2, C67.2, C68.2, C69.2, C70.2, C71.2, C72.2, C73.2, C74.2, C75.2, C76.2, C77.2, C78.2, C79.2, C80.2, C81.2, C82.2, C83.2, C84.2, C85.1, C86.2, C87.2, C88.1, C89.1, C90.1, D1.1, D2.1, D3.1, D4.1, D5.1, D6.1, D7.1, D8.1, D9.1, D10.1, D11.1, D12.1, D13.1, D14.1, D15.1, D16.1, D17.1, D18.1, D19.1, D20.1, D21.1, D22.1, D23.1, D24.1, D25.1, D26.1, D27.1, D28.1, D29.1, D30.1, D31.1, D32.1, D33.1, D34.1, D35.1, D36.1, D37.1, D38.1, D39.1, D40.1, D41.1, D42.1, D43.1, D44.1, D45.1, D46.1, D47.1, D48.1, D49.1, D50.1, D51.1, D52.1, D53.1, D54.1, D55.1, D56.1, D57.1, D58.1, D59.1, D60.1, D61.1, D62.1, D63.1, D64.1, D65.1, D66.1, D67.1, D68.1, D69.1, D70.1, D71.1, D72.1, D73.1, D74.1, D75.1, D76.1, D77.1, D78.1, D79.1, D80.1, D81.1, D82.1, D83.1, D84.1, J1.1, J2.1
GND: C1.1, C2.1, C3.1, C4.1, C5.1, C6.1, C7.1, C8.1, C9.1, C10.1, C11.1, C12.1, C13.1, C14.1, C15.1, C16.1, C17.1, C18.1, C19.1, C20.1, C21.1, C22.1, C23.1, C24.1, C25.1, C26.1, C27.1, C28.1, C29.2, C30.2, C31.2, C32.2, C33.2, C34.2, C35.2, C36.2, C37.2, C38.2, C39.2, C40.2, C41.2, C42.2, C43.2, C44.2, C45.2, C46.2, C47.2, C48.2, C49.2, C50.2, C51.2, C52.2, C53.2, C54.2, C55.2, C56.2, C57.1, C58.1, C59.1, C60.1, C61.1, C62.1, C63.1, C64.1, C65.1, C66.1, C67.1, C68.1, C69.1, C70.1, C71.1, C72.1, C73.1, C74.1, C75.1, C76.1, C77.1, C78.1, C79.1, C80.1, C81.1, C82.1, C83.1, C84.1, C85.2, C86.1, C87.1, C88.2, C89.2, C90.2, D1.3, D2.3, D3.3, D4.3, D5.3, D6.3, D7.3, D8.3, D9.3, D10.3, D11.3, D12.3, D13.3, D14.3, D15.3, D16.3, D17.3, D18.3, D19.3, D20.3, D21.3, D22.3, D23.3, D24.3, D25.3, D26.3, D27.3, D28.3, D29.3, D30.3, D31.3, D32.3, D33.3, D34.3, D35.3, D36.3, D37.3, D38.3, D39.3, D40.3, D41.3, D42.3, D43.3, D44.3, D45.3, D46.3, D47.3, D48.3, D49.3, D50.3, D51.3, D52.3, D53.3, D54.3, D55.3, D56.3, D57.3, D58.3, D59.3, D60.3, D61.3, D62.3, D63.3, D64.3, D65.3, D66.3, D67.3, D68.3, D69.3, D70.3, D71.3, D72.3, D73.3, D74.3, D75.3, D76.3, D77.3, D78.3, D79.3, D80.3, D81.3, D82.3, D83.3, D84.3, J1.3, J2.3
HDR_DIN: J1.2, R1.1
LED_D1: D1.2, D2.4
LED_D2: D2.2, D3.4
LED_D3: D3.2, D4.4
LED_D4: D4.2, D5.4
LED_D5: D5.2, D6.4
LED_D6: D6.2, D7.4
LED_D7: D7.2, D8.4
LED_D8: D8.2, D9.4
LED_D9: D9.2, D10.4
LED_D10: D10.2, D11.4
LED_D11: D11.2, D12.4
LED_D12: D12.2, D13.4
LED_D13: D13.2, D14.4
LED_D14: D14.2, D15.4
LED_D15: D15.2, D16.4
LED_D16: D16.2, D17.4
LED_D17: D17.2, D18.4
LED_D18: D18.2, D19.4
LED_D19: D19.2, D20.4
LED_D20: D20.2, D21.4
LED_D21: D21.2, D22.4
LED_D22: D22.2, D23.4
LED_D23: D23.2, D24.4
LED_D24: D24.2, D25.4
LED_D25: D25.2, D26.4
LED_D26: D26.2, D27.4
LED_D27: D27.2, D28.4
LED_D28: D28.2, D29.4
LED_D29: D29.2, D30.4
LED_D30: D30.2, D31.4
LED_D31: D31.2, D32.4
LED_D32: D32.2, D33.4
LED_D33: D33.2, D34.4
LED_D34: D34.2, D35.4
LED_D35: D35.2, D36.4
LED_D36: D36.2, D37.4
LED_D37: D37.2, D38.4
LED_D38: D38.2, D39.4
LED_D39: D39.2, D40.4
LED_D40: D40.2, D41.4
LED_D41: D41.2, D42.4
LED_D42: D42.2, D43.4
LED_D43: D43.2, D44.4
LED_D44: D44.2, D45.4
LED_D45: D45.2, D46.4
LED_D46: D46.2, D47.4
LED_D47: D47.2, D48.4
LED_D48: D48.2, D49.4
LED_D49: D49.2, D50.4
LED_D50: D50.2, D51.4
LED_D51: D51.2, D52.4
LED_D52: D52.2, D53.4
LED_D53: D53.2, D54.4
LED_D54: D54.2, D55.4
LED_D55: D55.2, D56.4
LED_D56: D56.2, D57.4
LED_D57: D57.2, D58.4
LED_D58: D58.2, D59.4
LED_D59: D59.2, D60.4
LED_D60: D60.2, D61.4
LED_D61: D61.2, D62.4
LED_D62: D62.2, D63.4
LED_D63: D63.2, D64.4
LED_D64: D64.2, D65.4
LED_D65: D65.2, D66.4
LED_D66: D66.2, D67.4
LED_D67: D67.2, D68.4
LED_D68: D68.2, D69.4
LED_D69: D69.2, D70.4
LED_D70: D70.2, D71.4
LED_D71: D71.2, D72.4
LED_D72: D72.2, D73.4
LED_D73: D73.2, D74.4
LED_D74: D74.2, D75.4
LED_D75: D75.2, D76.4
LED_D76: D76.2, D77.4
LED_D77: D77.2, D78.4
LED_D78: D78.2, D79.4
LED_D79: D79.2, D80.4
LED_D80: D80.2, D81.4
LED_D81: D81.2, D82.4
LED_D82: D82.2, D83.4
LED_D83: D83.2, D84.4
LED_DIN: D1.4, R1.2
LED_DOUT: D84.2, J2.2

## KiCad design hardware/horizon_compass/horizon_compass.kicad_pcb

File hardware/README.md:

# LunaNav physical twin

Physical companions to the app, generated from scripts so they can be rebuilt for any site.
**None of them has been manufactured yet.**

| | what | where |
|---|---|---|
| 1 | Terrain reliefs: Malapert Massif, and Shackleton ridge with de Gerlache rim | `relief/` |
| 2 | Horizon compass: 24-LED ring PCB, its printable stand, firmware sketch | `horizon_compass/` |
| 3 | Timeline bar: 3 × 28 LED PCB, three landing spots day by day | `timeline_bar/` |
| 4 | Site map: a PCB map of the south pole with an LED per Artemis III region | `site_map/` |
| 5 | Sky link: any ESP32 + NeoPixel ring mirrors the Sun and Earth around the rover you drive in the web app, live over USB (Web Serial) | `sky_link/` |

Pin mappings are checked against KiCad's own symbol library with `tools/kicad_pins.py`.

## 1. Terrain relief of Malapert Massif

The 24 × 24 km tile from the demo ("terrain beats latitude"), at **1:200,000 with true vertical scale**:
120 mm square, 24.2 mm of relief (4,845 m of real elevation range), 3 mm base.

| pin | point | elevation |
|---|---|---|
| A (red) | published point, 86°S 0°E | 4,795 m |
| B (yellow) | LunaNav derived point, 447 m NE | 4,851 m |
| C (green) | best point in the Artemis III region, 5 km W | 4,990 m |

Pins A and B are 2.2 mm apart on the model: that is how small the move is that takes Earth
visibility from 44 % to 100 %.

| file | what |
|---|---|
| `relief/malapert_massif.stl` | watertight solid, millimetres, 82,400 triangles: ready to slice |
| `relief/malapert_massif.json` | tile metadata and the model-space position of each point |
| `relief/malapert_massif.f3d` | Fusion archive: the mesh plus the three pins as solid bodies |

Rebuild, or make another tile (any site ids from `data/sites.yaml` / `data/derived_sites.yaml`):

```bash
# DEM: ldem_85s_40m.img + .lbl (115 MB) from
# https://pds-geosciences.wustl.edu/lro/lro-l-lola-3-rdr-v1/lrolol_1xxx/data/lola_gdr/polar/img/
python scripts/make_relief.py data/dem/ldem_85s_40m.img \
    --sites malapert_massif malapert_massif_derived malapert_massif_region_best \
    --size-km 24 --scale 200000 --out hardware/relief/malapert_massif
```

Orientation: +y points toward longitude 0 (the Earth-facing side), +x toward 90°E. The DEM orientation
was checked on Shackleton crater (floor at −2,788 m where expected; the mirrored coordinate gives +676 m).
Note this is the PDS `ldem_85s_40m` product, not the adjusted `LDEM_80S_40MPP_ADJ` grid the app's
horizons use, so elevations can differ by a few metres.

### Second tile: Shackleton connecting ridge and de Gerlache rim

The two classic near-pole candidates, 37.8 km apart, on one 48 × 48 km tile at **1:400,000 with true
vertical scale**: 120 mm square, 10.8 mm of relief (−2,353.5 m to 1,956 m), 3 mm base. In LunaNav's
data the ridge point has at least half the solar disk in view 91 % of the time and the rim point 77 %
(2026-11 → 2028-12).

| pin | point | elevation |
|---|---|---|
| red | Shackleton connecting ridge | 1,954.5 m |
| yellow | de Gerlache rim (site 011) | 1,810.5 m |

`relief/shackleton_ridge.stl` (82,400 triangles) and `.json` were made with `--sites shackleton_ridge
de_gerlache_rim --size-km 48 --scale 400000 --step 6`, which gives the same 0.6 mm model resolution as
the Malapert tile. The Fusion archive `relief/shackleton_ridge.f3d` was built from the same tile
sampled twice as finely (`--step 3`), so its pin heights differ from the JSON by about 0.02 mm.

## 2. Horizon compass (PCB)

A ring of 24 addressable LEDs, one per 15° of azimuth, around an ESP32-C3-DevKitM-1 that plugs into the
back. Idea: for a chosen site, light the LED in the Sun's direction yellow and the Earth's direction
blue, brightness following elevation above the terrain horizon, and replay a lunar day in seconds.

- 78 mm round, 2 layers, ground pour on both sides
- D1–D24 WS2812B (5050), C1–C24 100 nF, C25 10 µF, R1 330 Ω in the data line
- The whole board is generated by `horizon_compass/generate_board.py` (KiCad Python API)
- `horizon_compass/horizon_compass.step`: the board as a STEP solid, for CAD

```bash
cd hardware/horizon_compass
"C:/Program Files/KiCad/10.0/bin/python.exe" generate_board.py
kicad-cli pcb drc --refill-zones --save-board horizon_compass.kicad_pcb   # fills the ground pours
```

**Status: layout concept, not ready to order.** KiCad 10.0.4 DRC reports 0 violations and 0 unconnected
items, but:

- There is no schematic; the netlist lives in the script.
- The DevKitM-1 pin numbers (5V = 13/14, data = pin 11 / IO10, ten grounds) are checked against KiCad's
  own symbol with `tools/kicad_pins.py`; that check caught IO6 tied to ground in the first draft. The
  footprint has not been checked against a physical devkit yet.
- 3.3 V data into 5 V WS2812B usually works but is out of spec; add a level shifter if it flickers.
- All 24 LEDs at full white draw about 1.4 A, more than USB through the devkit can supply. The intended
  use lights two LEDs; firmware must cap brightness.
- The ground pour runs under the devkit's antenna; add a keep-out there.
- The LED chain runs counter-clockwise from D1 (north). Two M3 mounting holes sit left and right of the devkit.

### Firmware and data

`scripts/export_compass_track.py` turns any site's precomputed series into `firmware/track.h`: per hour,
the LED facing the Sun, its brightness (visible fraction of the solar disk above the terrain) and the LED
facing Earth (lit while Earth's centre is above the terrain). `firmware/firmware.ino` (Arduino core for
ESP32, Adafruit NeoPixel) replays it at one hour per frame, so 30 days take about a minute.

```bash
python scripts/export_compass_track.py malapert_massif --start 2027-09-09 --days 30               # committed default
python scripts/export_compass_track.py malapert_massif_region_best --start 2027-09-09 --days 30   # 5 km west
```

Same 30 days, two spots 5 km apart: at the published point the Sun LED is lit in 64 % of the 720 frames
and the Earth LED in 40 %; at the best point in the region both stay on in every frame. **The firmware
has not been compiled or run on hardware yet.**

### Stand

A two-part printable stand modelled in Fusion: a base cup the board screws into (82.6 mm outer
diameter, 20.6 mm tall, two posts under the M3 holes, a cable slot at each end of the devkit) and a
diffuser ring that rests on the rim over the LEDs. Dimensions, the clearances measured in CAD and the
list of what is unverified are in [horizon_compass/enclosure/README.md](horizon_compass/enclosure/README.md).
Never printed or test-fitted.

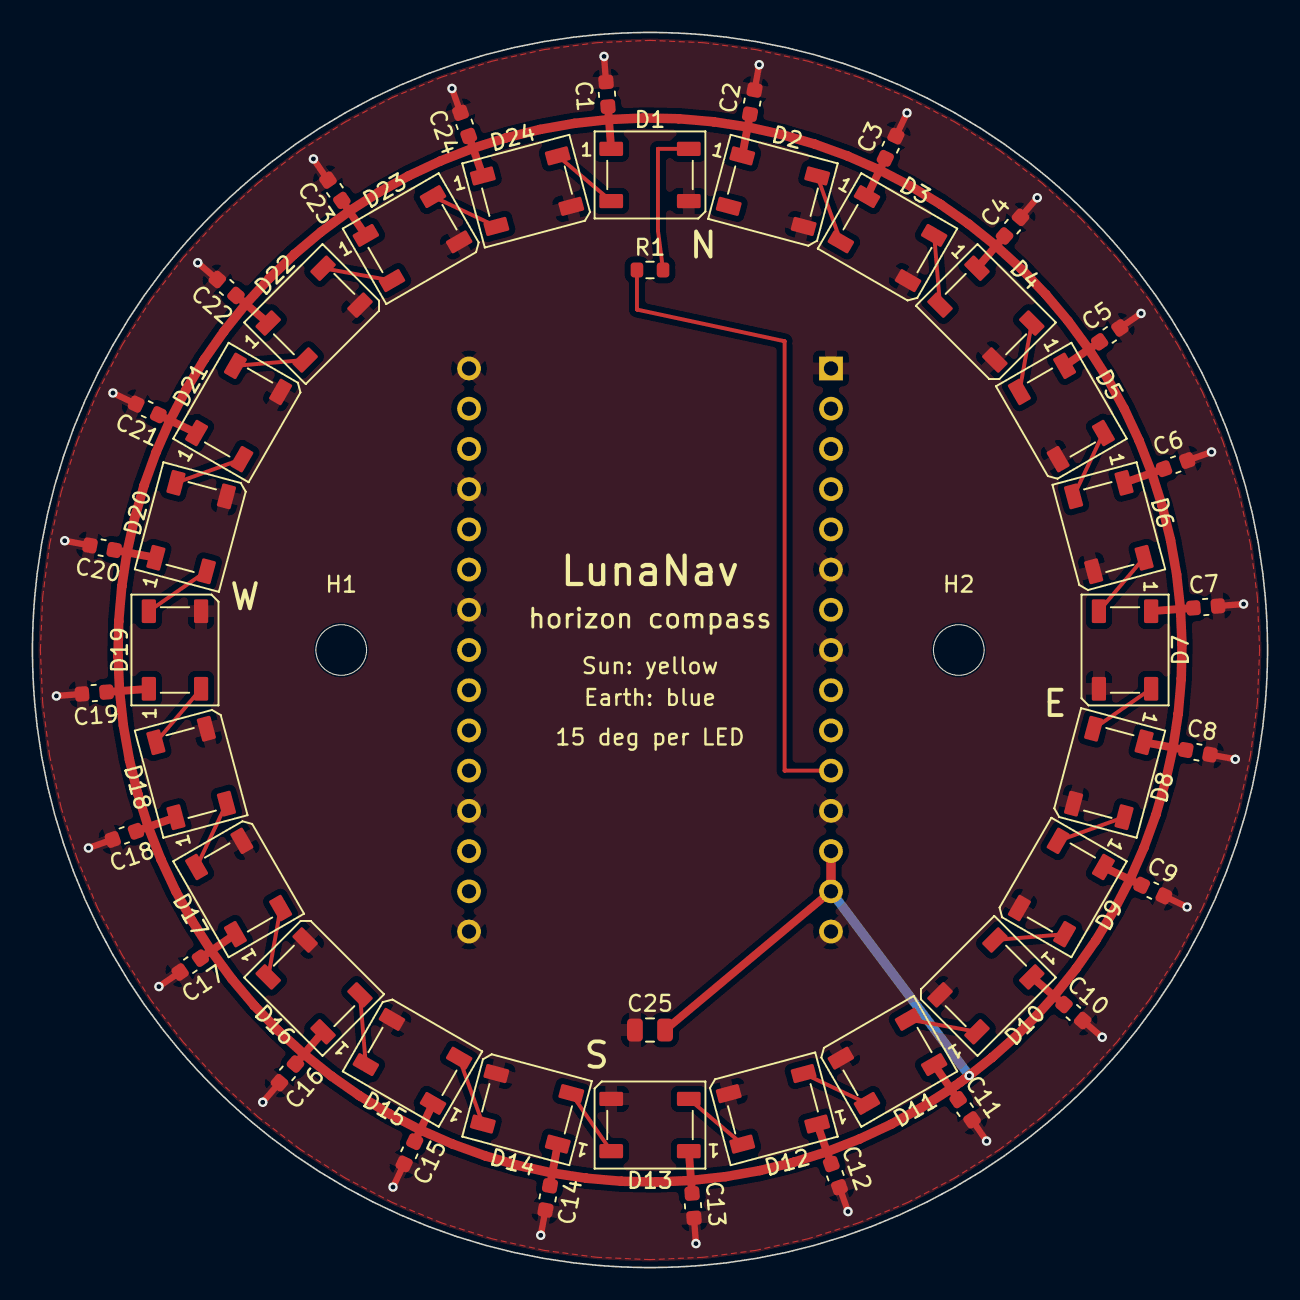
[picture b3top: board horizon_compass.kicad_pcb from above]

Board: 2 copper layers, 78.0 x 78.0 mm, 53 parts (1 on the bottom side), 27 nets.

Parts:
A1: ESP32-C3-DevKitM-1
C1, C2, C3, C4, C5, C6, C7, C8, C9, C10, C11, C12, C13, C14, C15, C16, C17, C18, C19, C20, C21, C22, C23, C24: 100n; C_0603_1608Metric
C25: 10u; C_0805_2012Metric
D1, D2, D3, D4, D5, D6, D7, D8, D9, D10, D11, D12, D13, D14, D15, D16, D17, D18, D19, D20, D21, D22, D23, D24: WS2812B; LED_WS2812B_PLCC4_5.0x5.0mm_P3.2mm
H1, H2: M3; MountingHole_3.2mm_M3
R1: 330R; R_0603_1608Metric

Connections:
+5V: A1.13, A1.14, C1.1, C2.1, C3.1, C4.1, C5.1, C6.1, C7.1, C8.1, C9.1, C10.1, C11.1, C12.1, C13.1, C14.1, C15.1, C16.1, C17.1, C18.1, C19.1, C20.1, C21.1, C22.1, C23.1, C24.1, C25.2, D1.1, D2.1, D3.1, D4.1, D5.1, D6.1, D7.1, D8.1, D9.1, D10.1, D11.1, D12.1, D13.1, D14.1, D15.1, D16.1, D17.1, D18.1, D19.1, D20.1, D21.1, D22.1, D23.1, D24.1
GND: A1.1, A1.6, A1.8, A1.12, A1.15, A1.16, A1.19, A1.24, A1.27, A1.30, C1.2, C2.2, C3.2, C4.2, C5.2, C6.2, C7.2, C8.2, C9.2, C10.2, C11.2, C12.2, C13.2, C14.2, C15.2, C16.2, C17.2, C18.2, C19.2, C20.2, C21.2, C22.2, C23.2, C24.2, C25.1, D1.3, D2.3, D3.3, D4.3, D5.3, D6.3, D7.3, D8.3, D9.3, D10.3, D11.3, D12.3, D13.3, D14.3, D15.3, D16.3, D17.3, D18.3, D19.3, D20.3, D21.3, D22.3, D23.3, D24.3
LED_D1: D1.2, D24.4
LED_D2: D23.4, D24.2
LED_D3: D22.4, D23.2
LED_D4: D21.4, D22.2
LED_D5: D20.4, D21.2
LED_D6: D19.4, D20.2
LED_D7: D18.4, D19.2
LED_D8: D17.4, D18.2
LED_D9: D16.4, D17.2
LED_D10: D15.4, D16.2
LED_D11: D14.4, D15.2
LED_D12: D13.4, D14.2
LED_D13: D12.4, D13.2
LED_D14: D11.4, D12.2
LED_D15: D10.4, D11.2
LED_D16: D9.4, D10.2
LED_D17: D8.4, D9.2
LED_D18: D7.4, D8.2
LED_D19: D6.4, D7.2
LED_D20: D5.4, D6.2
LED_D21: D4.4, D5.2
LED_D22: D3.4, D4.2
LED_D23: D2.4, D3.2
LED_DIN: D1.4, R1.2
LED_GPIO: A1.11, R1.1

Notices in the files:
README.md:
License:
See `LICENSE`.
